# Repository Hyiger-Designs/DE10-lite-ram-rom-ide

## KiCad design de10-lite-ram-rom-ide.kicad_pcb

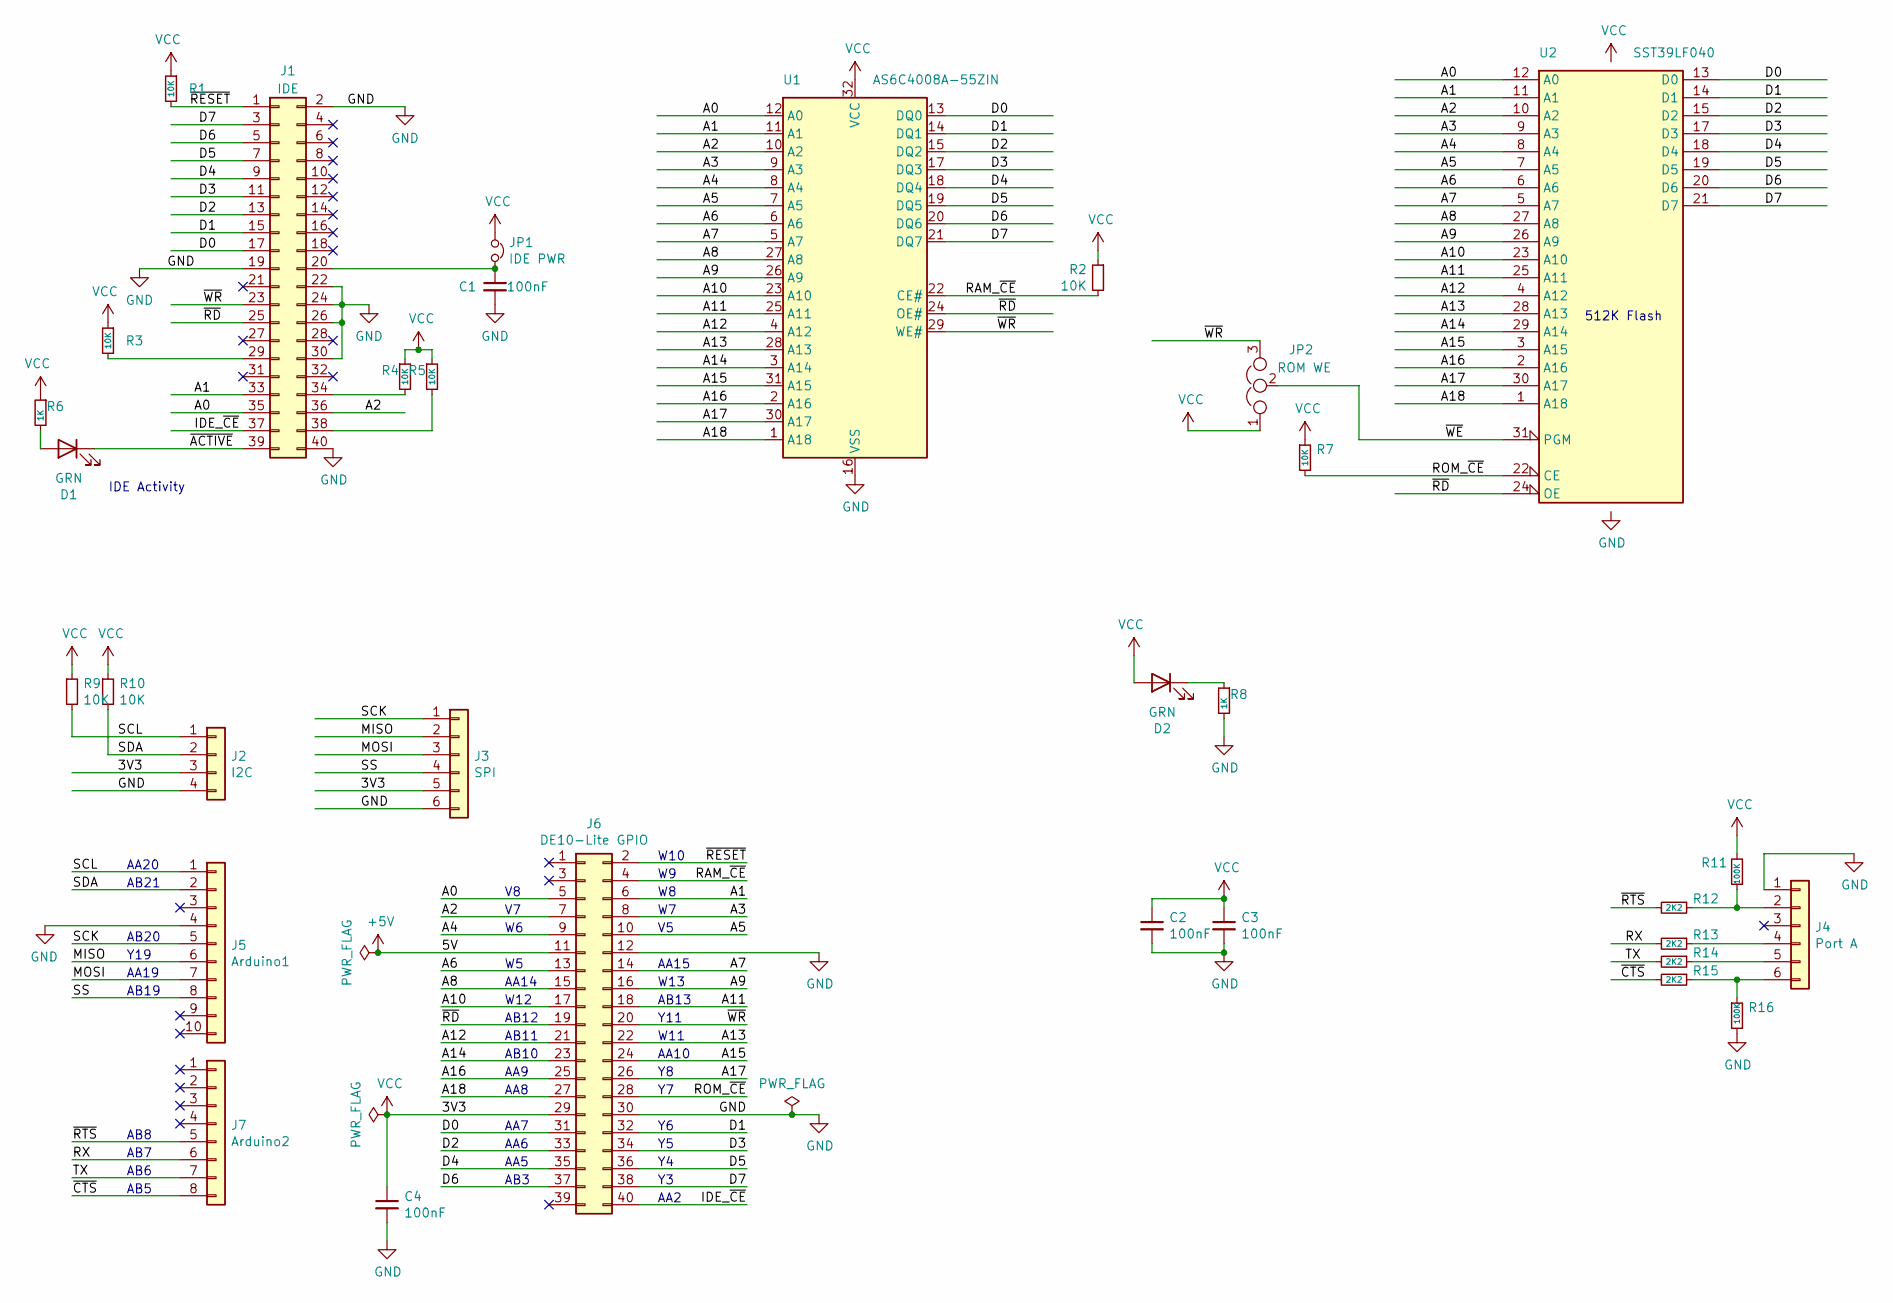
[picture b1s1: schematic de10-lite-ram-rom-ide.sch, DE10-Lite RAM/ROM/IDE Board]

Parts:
C1: 100nF; C_0603_1608Metric_Pad1.05x0.95mm_HandSolder; MPN JMK107B7474KA-T
C2, C3, C4: 100nF; C_0603_1608Metric_Pad1.05x0.95mm_HandSolder
D1, D2: GRN; LED_0603_1608Metric_Pad1.05x0.95mm_HandSolder
J1: IDE; PinHeader_2x20_P2.54mm_Horizontal
J2: I2C; PinHeader_1x04_P2.54mm_Vertical
J3: SPI; PinHeader_1x06_P2.54mm_Vertical
J4: Port A; PinHeader_1x06_P2.54mm_Horizontal
J5: Arduino1; PinHeader_1x10_P2.54mm_Vertical
J6: DE10-Lite GPIO; PinSocket_2x20_P2.54mm_Vertical
J7: Arduino2; PinHeader_1x08_P2.54mm_Vertical
JP1: IDE PWR; PinHeader_1x02_P2.54mm_Vertical
JP2: ROM WE; PinHeader_1x03_P2.54mm_Vertical
R1, R2, R3, R4, R5, R7, R9, R10: 10K; R_0603_1608Metric_Pad1.05x0.95mm_HandSolder
R6, R8: 1K; R_0603_1608Metric_Pad1.05x0.95mm_HandSolder
R11, R16: 100K; R_0603_1608Metric_Pad1.05x0.95mm_HandSolder
R12, R13, R14, R15: 2K2; R_0603_1608Metric_Pad1.05x0.95mm_HandSolder
U1: AS6C4008A-55ZIN; TSOP-II-32_21.0x10.2mm_P1.27mm
U2: SST39LF040; PLCC-32_11.4x14.0mm_P1.27mm; MPN SST39LF040-55-4C-NHE-T

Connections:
+5V: J6.11
/A0: J1.35, J6.5, U1.12 (A0), U2.12 (A0)
/A1: J1.33, J6.6, U1.11 (A1), U2.11 (A1)
/A2: J1.36, J6.7, U1.10 (A2), U2.10 (A2)
/A3: J6.8, U1.9 (A3), U2.9 (A3)
/A4: J6.9, U1.8 (A4), U2.8 (A4)
/A5: J6.10, U1.7 (A5), U2.7 (A5)
/A6: J6.13, U1.6 (A6), U2.6 (A6)
/A7: J6.14, U1.5 (A7), U2.5 (A7)
/A8: J6.15, U1.27 (A8), U2.27 (A8)
/A9: J6.16, U1.26 (A9), U2.26 (A9)
/A10: J6.17, U1.23 (A10), U2.23 (A10)
/A11: J6.18, U1.25 (A11), U2.25 (A11)
/A12: J6.21, U1.4 (A12), U2.4 (A12)
/A13: J6.22, U1.28 (A13), U2.28 (A13)
/A14: J6.23, U1.3 (A14), U2.29 (A14)
/A15: J6.24, U1.31 (A15), U2.3 (A15)
/A16: J6.25, U1.2 (A16), U2.2 (A16)
/A17: J6.26, U1.30 (A17), U2.30 (A17)
/A18: J6.27, U1.1 (A18), U2.1 (A18)
/D0: J1.17, J6.31, U1.13 (DQ0), U2.13 (D0)
/D1: J1.15, J6.32, U1.14 (DQ1), U2.14 (D1)
/D2: J1.13, J6.33, U1.15 (DQ2), U2.15 (D2)
/D3: J1.11, J6.34, U1.17 (DQ3), U2.17 (D3)
/D4: J1.9, J6.35, U1.18 (DQ4), U2.18 (D4)
/D5: J1.7, J6.36, U1.19 (DQ5), U2.19 (D5)
/D6: J1.5, J6.37, U1.20 (DQ6), U2.20 (D6)
/D7: J1.3, J6.38, U1.21 (DQ7), U2.21 (D7)
/IDE_~CE~: J1.37, J6.40
/MISO: J3.2, J5.6
/MOSI: J3.3, J5.7
/RAM_~CE: J6.4, R2.2, U1.22 (CE#)
/ROM_~CE: J6.28, R7.2, U2.22 (CE)
/RX: J7.6, R13.2
/SCK: J3.1, J5.5
/SCL: J2.1, J5.1, R9.2
/SDA: J2.2, J5.2, R10.2
/SS: J3.4, J5.8
/TX: J7.7, R14.2
/~ACTIVE: D1.1 (K), J1.39
/~CTS: J7.8, R15.2
/~RD: J1.25, J6.19, U1.24 (OE#), U2.24 (OE)
/~RESET: J1.1, J6.2, R1.2
/~RTS: J7.5, R12.2
/~WE: JP2.2, U2.31 (PGM)
/~WR: J1.23, J6.20, JP2.3, U1.29 (WE#)
GND: C1.2, C2.2, C3.2, C4.2, J1.2, J1.19, J1.22, J1.24, J1.26, J1.30, J1.40, J2.4, J3.6, J4.1, J5.4, J6.12, J6.30, R8.2, R16.2, U1.16 (VSS), U2.16 (GND)
unnamed: C1.1, J1.20, JP1.2
unnamed: D1.2 (A), R6.2
unnamed: D2.1 (K), R8.1
unnamed: J1.29, R3.2
unnamed: J1.34, R4.2
unnamed: J1.38, R5.2
unnamed: J4.2, R11.1, R12.1
unnamed: J4.4, R13.1
unnamed: J4.5, R14.1
unnamed: J4.6, R15.1, R16.1
VCC: C2.1, C3.1, C4.1, D2.2 (A), J2.3, J3.5, J6.29, JP1.1, JP2.1, R1.1, R2.1, R3.1, R4.1, R5.1, R6.1, R7.1, R9.1, R10.1, R11.2, U1.32 (VCC), U2.32 (VCC)

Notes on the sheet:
512K Flash
IDE Activity
AA14
W10
AA15
W13
AB13
Y11
AA2
W12
AB20
Y19
AA19
AB19
AB8
AB7
AB6
AB5
AB21
AA20
AB3
AA5
AA6
AA7
AA10
W11
AA8
AA9
AB10
AB11
AB12

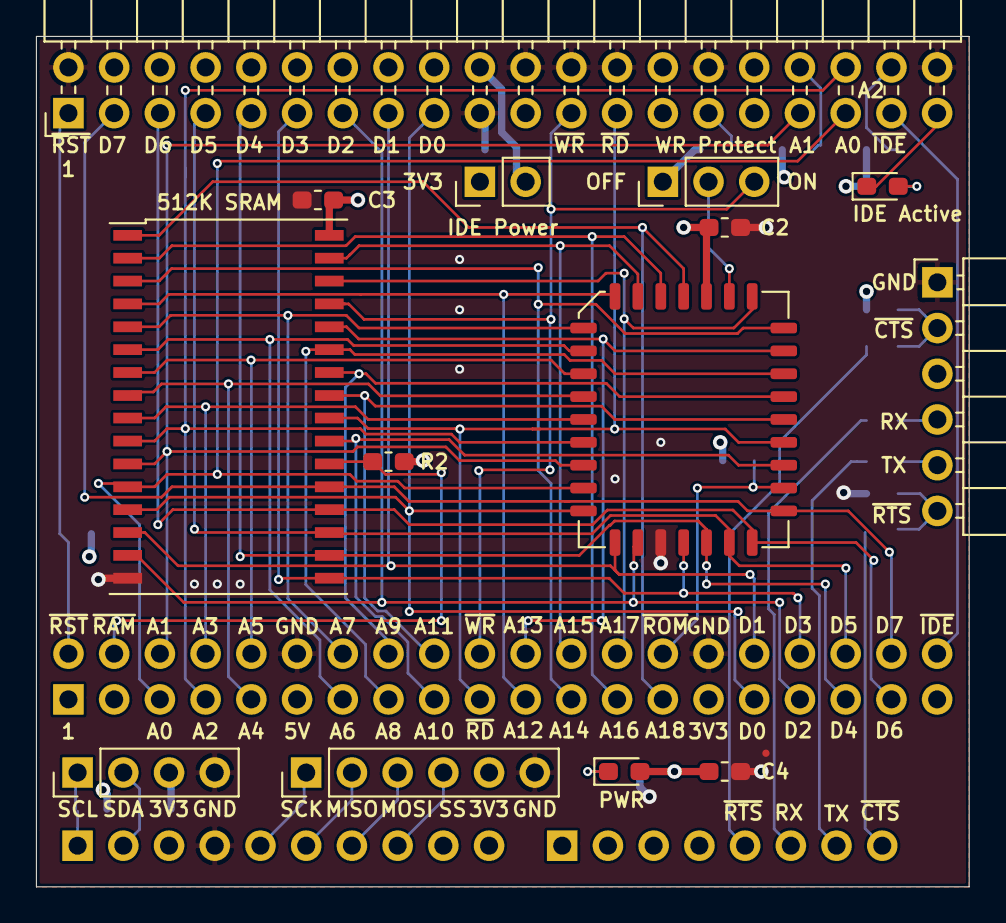
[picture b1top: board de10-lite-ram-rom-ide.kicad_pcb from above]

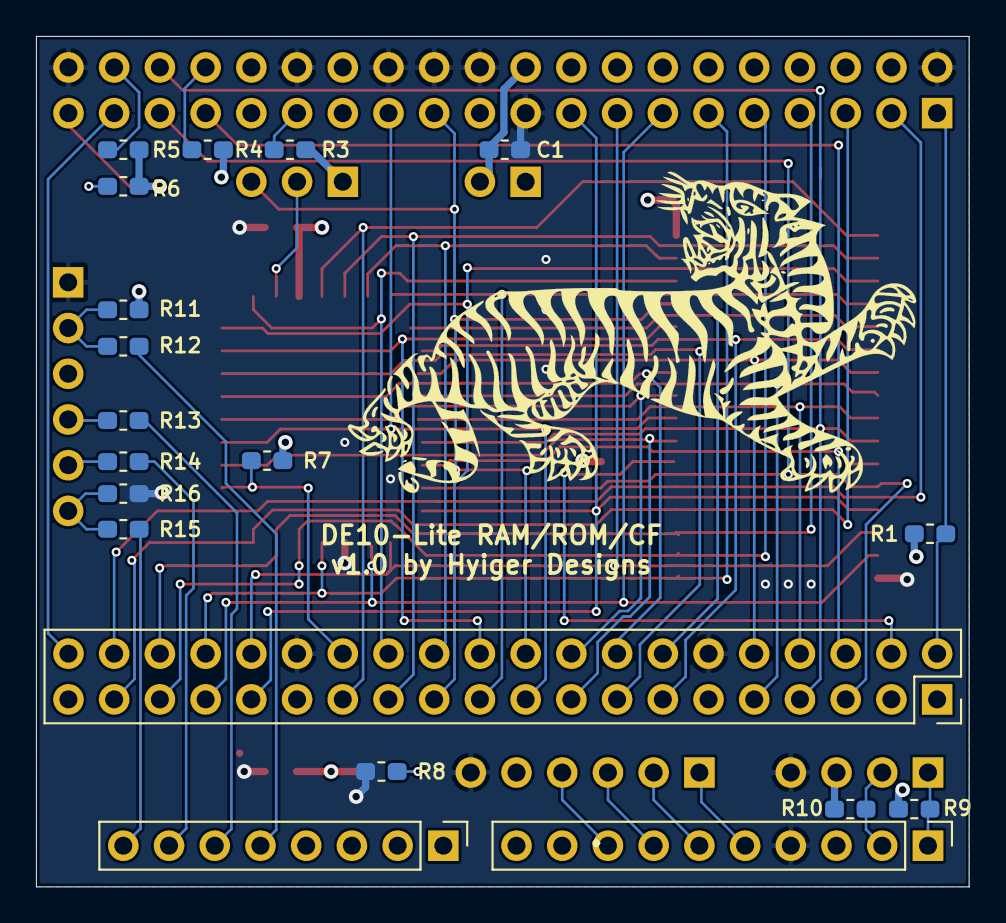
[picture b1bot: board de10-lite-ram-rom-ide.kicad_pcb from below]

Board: 4 copper layers, 51.8 x 47.2 mm, 33 parts (19 on the bottom side), 57 nets.

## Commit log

2020-02-27 Initial version 1.0
